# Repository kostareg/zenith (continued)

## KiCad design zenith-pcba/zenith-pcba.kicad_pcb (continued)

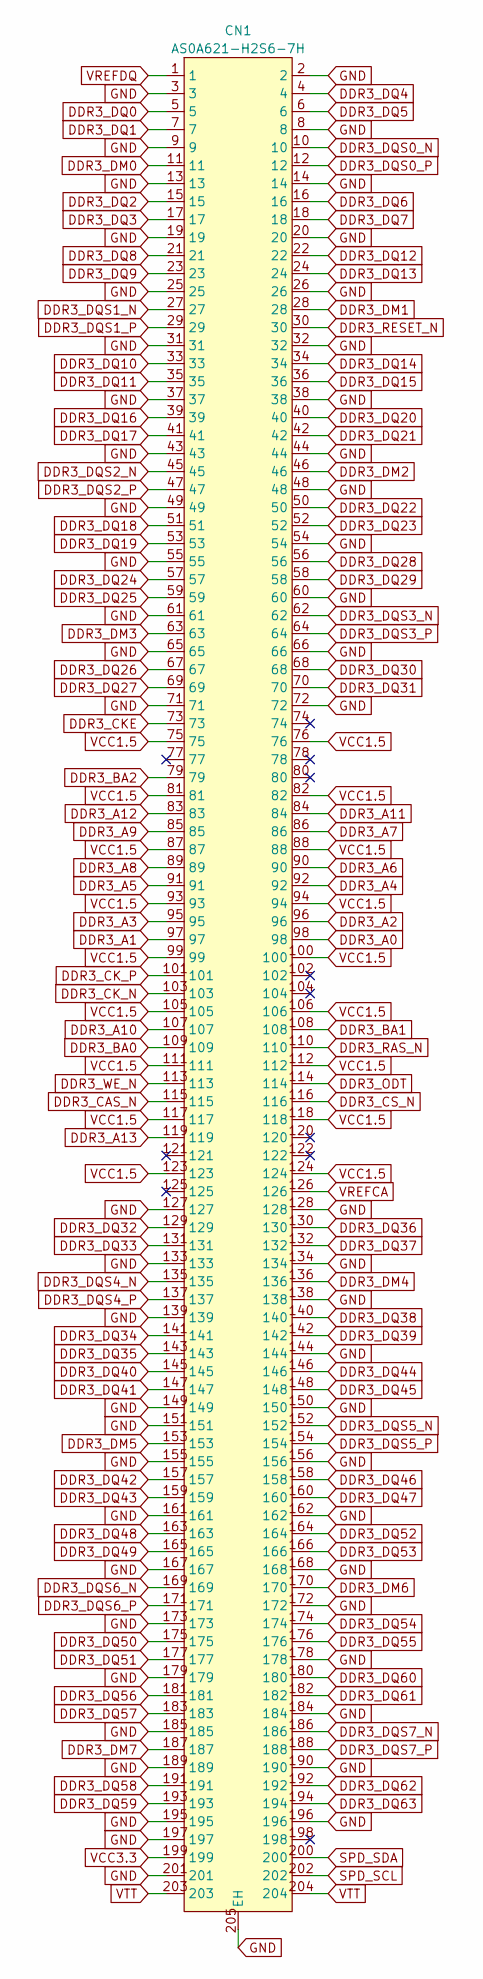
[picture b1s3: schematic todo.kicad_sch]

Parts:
CN1: AS0A621-H2S6-7H; CONN-SMD_204P-P0.60_AS0A621-H2S6-7H; MPN AS0A621-H2S6-7H; LCSC Part C225721

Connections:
DDR3_A0: CN1.98; also elsewhere on the board
DDR3_A1: CN1.97; also elsewhere on the board
DDR3_A2: CN1.96; also elsewhere on the board
DDR3_A3: CN1.95; also elsewhere on the board
DDR3_A4: CN1.92; also elsewhere on the board
DDR3_A5: CN1.91; also elsewhere on the board
DDR3_A6: CN1.90; also elsewhere on the board
DDR3_A7: CN1.86; also elsewhere on the board
DDR3_A8: CN1.89; also elsewhere on the board
DDR3_A9: CN1.85; also elsewhere on the board
DDR3_A10: CN1.107; also elsewhere on the board
DDR3_A11: CN1.84; also elsewhere on the board
DDR3_A12: CN1.83; also elsewhere on the board
DDR3_A13: CN1.119; also elsewhere on the board
DDR3_BA0: CN1.109; also elsewhere on the board
DDR3_BA1: CN1.108; also elsewhere on the board
DDR3_BA2: CN1.79; also elsewhere on the board
DDR3_CAS_N: CN1.115; also elsewhere on the board
DDR3_CKE: CN1.73; also elsewhere on the board
DDR3_CK_N: CN1.103; also elsewhere on the board
DDR3_CK_P: CN1.101; also elsewhere on the board
DDR3_CS_N: CN1.116; also elsewhere on the board
DDR3_DM0: CN1.11; also elsewhere on the board
DDR3_DM1: CN1.28; also elsewhere on the board
DDR3_DM2: CN1.46; also elsewhere on the board
DDR3_DM3: CN1.63; also elsewhere on the board
DDR3_DM4: CN1.136; also elsewhere on the board
DDR3_DM5: CN1.153; also elsewhere on the board
DDR3_DM6: CN1.170; also elsewhere on the board
DDR3_DM7: CN1.187; also elsewhere on the board
DDR3_DQ0: CN1.5; also elsewhere on the board
DDR3_DQ1: CN1.7; also elsewhere on the board
DDR3_DQ2: CN1.15; also elsewhere on the board
DDR3_DQ3: CN1.17; also elsewhere on the board
DDR3_DQ4: CN1.4; also elsewhere on the board
DDR3_DQ5: CN1.6; also elsewhere on the board
DDR3_DQ6: CN1.16; also elsewhere on the board
DDR3_DQ7: CN1.18; also elsewhere on the board
DDR3_DQ8: CN1.21; also elsewhere on the board
DDR3_DQ9: CN1.23; also elsewhere on the board
DDR3_DQ10: CN1.33; also elsewhere on the board
DDR3_DQ11: CN1.35; also elsewhere on the board
DDR3_DQ12: CN1.22; also elsewhere on the board
DDR3_DQ13: CN1.24; also elsewhere on the board
DDR3_DQ14: CN1.34; also elsewhere on the board
DDR3_DQ15: CN1.36; also elsewhere on the board
DDR3_DQ16: CN1.39; also elsewhere on the board
DDR3_DQ17: CN1.41; also elsewhere on the board
DDR3_DQ18: CN1.51; also elsewhere on the board
DDR3_DQ19: CN1.53; also elsewhere on the board
DDR3_DQ20: CN1.40; also elsewhere on the board
DDR3_DQ21: CN1.42; also elsewhere on the board
DDR3_DQ22: CN1.50; also elsewhere on the board
DDR3_DQ23: CN1.52; also elsewhere on the board
DDR3_DQ24: CN1.57; also elsewhere on the board
DDR3_DQ25: CN1.59; also elsewhere on the board
DDR3_DQ26: CN1.67; also elsewhere on the board
DDR3_DQ27: CN1.69; also elsewhere on the board
DDR3_DQ28: CN1.56; also elsewhere on the board
DDR3_DQ29: CN1.58; also elsewhere on the board
DDR3_DQ30: CN1.68; also elsewhere on the board
DDR3_DQ31: CN1.70; also elsewhere on the board
DDR3_DQ32: CN1.129; also elsewhere on the board
DDR3_DQ33: CN1.131; also elsewhere on the board
DDR3_DQ34: CN1.141; also elsewhere on the board
DDR3_DQ35: CN1.143; also elsewhere on the board
DDR3_DQ36: CN1.130; also elsewhere on the board
DDR3_DQ37: CN1.132; also elsewhere on the board
DDR3_DQ38: CN1.140; also elsewhere on the board
DDR3_DQ39: CN1.142; also elsewhere on the board
DDR3_DQ40: CN1.145; also elsewhere on the board
DDR3_DQ41: CN1.147; also elsewhere on the board
DDR3_DQ42: CN1.157; also elsewhere on the board
DDR3_DQ43: CN1.159; also elsewhere on the board
DDR3_DQ44: CN1.146; also elsewhere on the board
DDR3_DQ45: CN1.148; also elsewhere on the board
DDR3_DQ46: CN1.158; also elsewhere on the board
DDR3_DQ47: CN1.160; also elsewhere on the board
DDR3_DQ48: CN1.163; also elsewhere on the board
DDR3_DQ49: CN1.165; also elsewhere on the board
DDR3_DQ50: CN1.175; also elsewhere on the board
DDR3_DQ51: CN1.177; also elsewhere on the board
DDR3_DQ52: CN1.164; also elsewhere on the board
DDR3_DQ53: CN1.166; also elsewhere on the board
DDR3_DQ54: CN1.174; also elsewhere on the board
DDR3_DQ55: CN1.176; also elsewhere on the board
DDR3_DQ56: CN1.181; also elsewhere on the board
DDR3_DQ57: CN1.183; also elsewhere on the board
DDR3_DQ58: CN1.191; also elsewhere on the board
DDR3_DQ59: CN1.193; also elsewhere on the board
DDR3_DQ60: CN1.180; also elsewhere on the board
DDR3_DQ61: CN1.182; also elsewhere on the board
DDR3_DQ62: CN1.192; also elsewhere on the board
DDR3_DQ63: CN1.194; also elsewhere on the board
DDR3_DQS0_N: CN1.10; also elsewhere on the board
DDR3_DQS0_P: CN1.12; also elsewhere on the board
DDR3_DQS1_N: CN1.27; also elsewhere on the board
DDR3_DQS1_P: CN1.29; also elsewhere on the board
DDR3_DQS2_N: CN1.45; also elsewhere on the board
DDR3_DQS2_P: CN1.47; also elsewhere on the board
DDR3_DQS3_N: CN1.62; also elsewhere on the board
DDR3_DQS3_P: CN1.64; also elsewhere on the board
DDR3_DQS4_N: CN1.135; also elsewhere on the board
DDR3_DQS4_P: CN1.137; also elsewhere on the board
DDR3_DQS5_N: CN1.152; also elsewhere on the board
DDR3_DQS5_P: CN1.154; also elsewhere on the board
DDR3_DQS6_N: CN1.169; also elsewhere on the board
DDR3_DQS6_P: CN1.171; also elsewhere on the board
DDR3_DQS7_N: CN1.186; also elsewhere on the board
DDR3_DQS7_P: CN1.188; also elsewhere on the board
DDR3_ODT: CN1.114; also elsewhere on the board
DDR3_RAS_N: CN1.110; also elsewhere on the board
DDR3_RESET_N: CN1.30; also elsewhere on the board
DDR3_WE_N: CN1.113; also elsewhere on the board
GND: CN1.2, CN1.3, CN1.8, CN1.9, CN1.13, CN1.14, CN1.19, CN1.20, CN1.25, CN1.26, CN1.31, CN1.32, CN1.37, CN1.38, CN1.43, CN1.44, CN1.48, CN1.49, CN1.54, CN1.55, CN1.60, CN1.61, CN1.65, CN1.66, CN1.71, CN1.72, CN1.127, CN1.128, CN1.133, CN1.134, CN1.138, CN1.139, CN1.144, CN1.149, CN1.150, CN1.151, CN1.155, CN1.156, CN1.161, CN1.162, CN1.167, CN1.168, CN1.172, CN1.173, CN1.178, CN1.179, CN1.184, CN1.185, CN1.189, CN1.190, CN1.195, CN1.196, CN1.197, CN1.201, CN1.205 (EH); also elsewhere on the board
SPD_SCL: CN1.202
SPD_SDA: CN1.200
VCC1.5: CN1.75, CN1.76, CN1.81, CN1.82, CN1.87, CN1.88, CN1.93, CN1.94, CN1.99, CN1.100, CN1.105, CN1.106, CN1.111, CN1.112, CN1.117, CN1.118, CN1.123, CN1.124
VCC3.3: CN1.199; also elsewhere on the board
VREFCA: CN1.126
VREFDQ: CN1.1
VTT: CN1.203, CN1.204

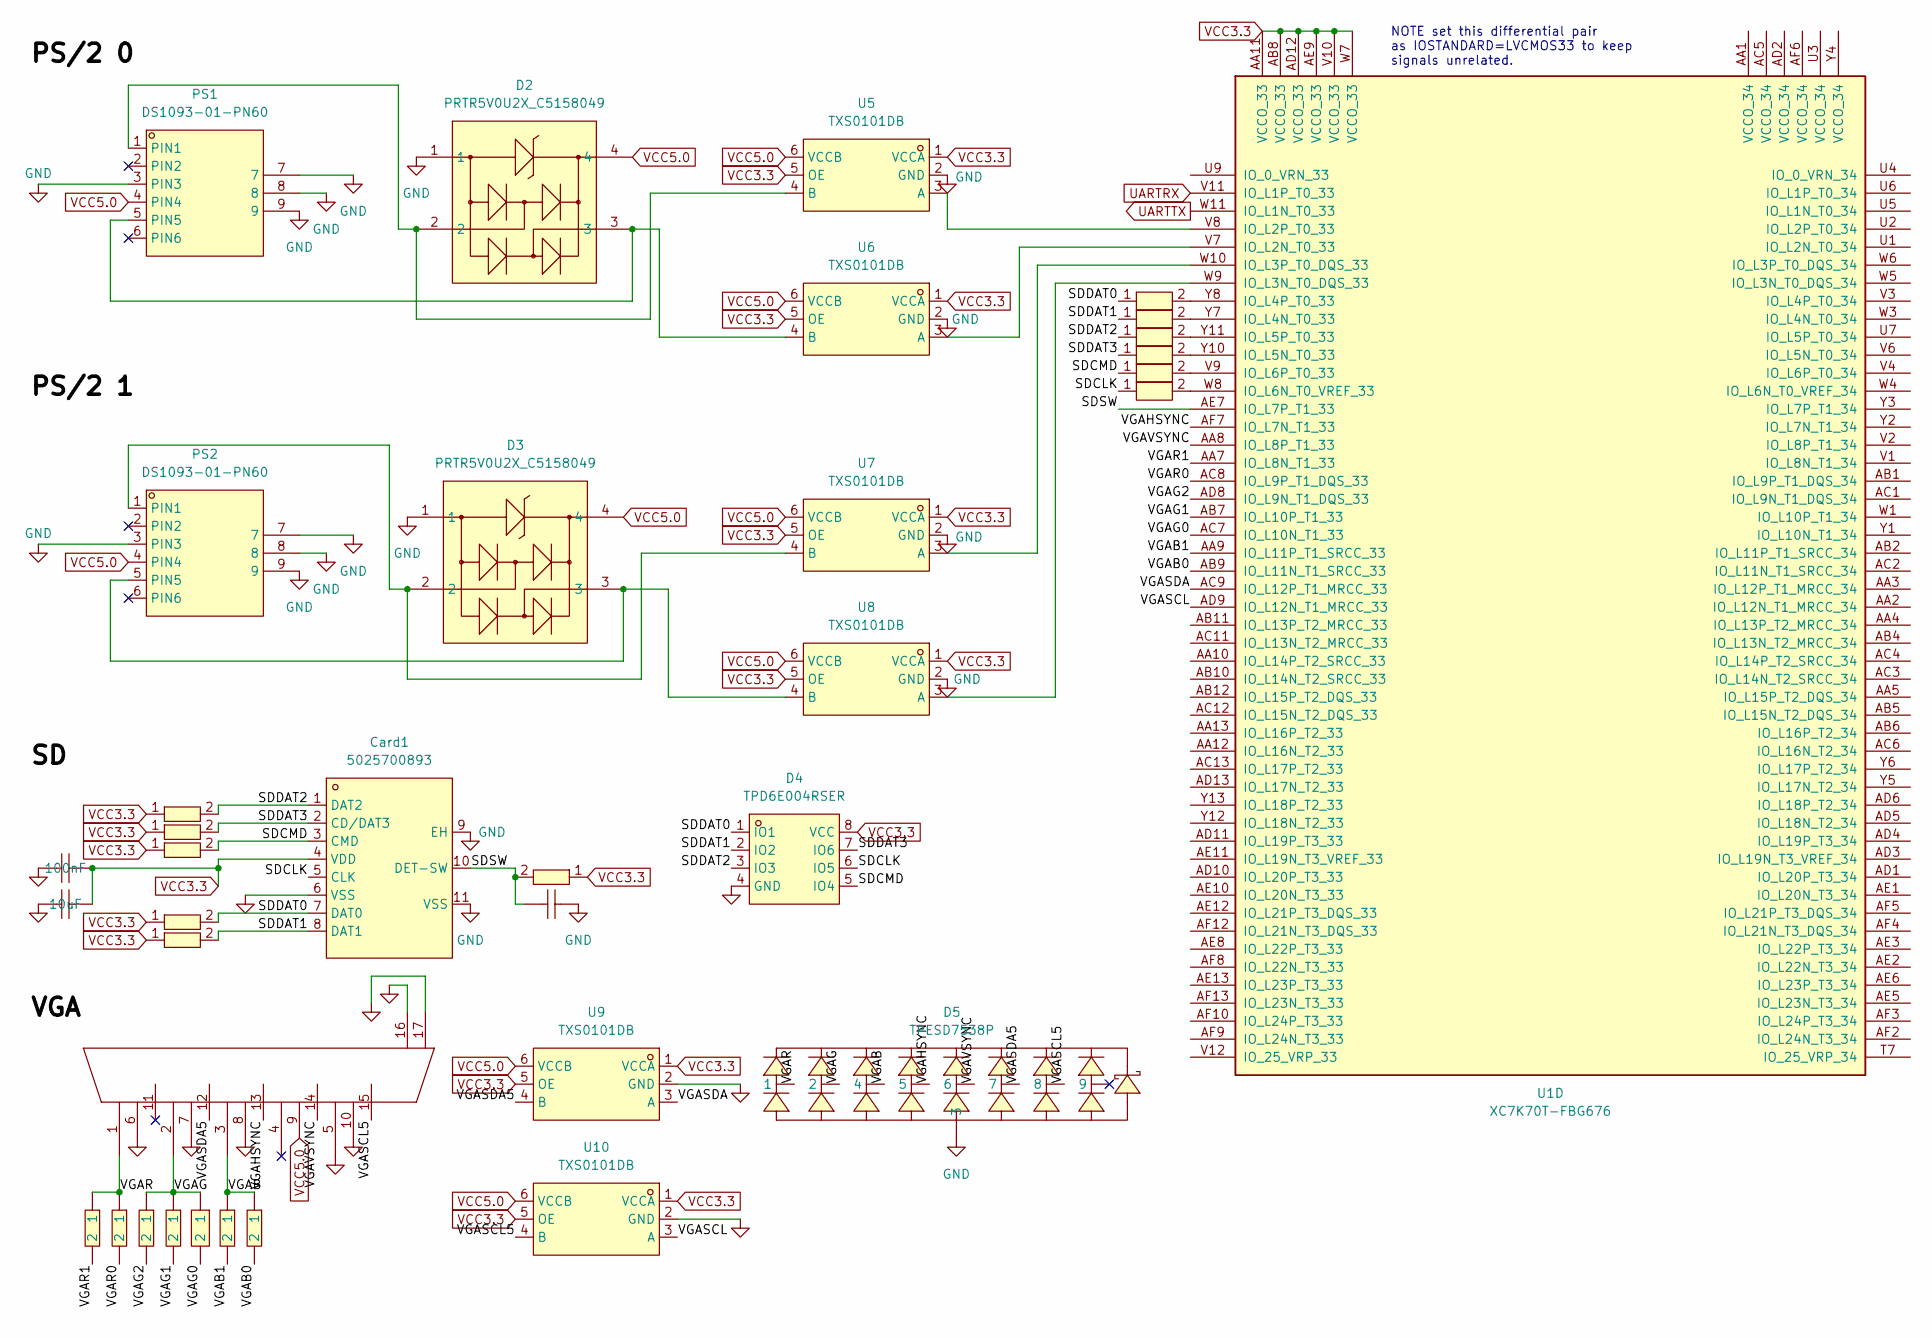
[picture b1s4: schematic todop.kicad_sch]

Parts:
C8, C9: CL10B104KA8NNNC; C0603; MPN CL10B104KA8NNNC; LCSC Part C1590
C10: CC0603MRX5R7BB106; C0603; MPN CC0603MRX5R7BB106; LCSC Part C109457
Card1: 5025700893; TF-SMD_5025700893; MPN 5025700893; LCSC Part C429846
D2, D3: PRTR5V0U2X_C5158049; SOT-143_L2.9-W1.3-P1.92-LS2.3-BL; MPN PRTR5V0U2X; LCSC Part C5158049
D4: TPD6E004RSER; UQFN-8_L1.5-W1.5-P0.50-TL; MPN TPD6E004RSER; LCSC Part C1973052
D5: TPESD7538P; DFN3810-9_L3.8-W1.0-P0.9; MPN TPESD7538P; LCSC Part C970014
DSub1: DS1038-15FBNSIA74-0CC; DSUB-TH_DS1038-15FBNSIA74-0CC; MPN DS1038-15FBNSiA74-0CC; LCSC Part C75754
PS1, PS2: DS1093-01-PN60; CONN-TH_DS1093-01-PN60; MPN DS1093-01-PN60; LCSC Part C77848
R5, R6, R7, R8, R9, R16: RC0402FR-0710KL; R0402; MPN RC0402FR-0710KL; LCSC Part C60490
R10, R11, R12, R13, R14, R15: RC0402FR-0722R1L; R0402; MPN RC0402FR-0722R1L; LCSC Part C327363
R17, R19, R21: RC0402JR-07510RL; R0402; MPN RC0402JR-07510RL; LCSC Part C137860
R18, R20, R22: RC0402FR-071K02L; R0402; MPN RC0402FR-071K02L; LCSC Part C163485
R23: RC0402DR-072K05L; R0402; MPN RC0402DR-072K05L; LCSC Part C471776
U1: XC7K70T-FBG676; FBGA-676_L27.0-W27.0-R26-C26-P1.00-BL
U5, U6, U7, U8, U9, U10: TXS0101DB; SOT-23-6_L2.9-W1.6-P0.95-LS2.9-BL; MPN TXS0101DB(LX); LCSC Part C22469953

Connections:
/IO/SDCLK: Card1.5 (CLK), D4.6 (IO5), R15.1
/IO/SDCMD: Card1.3 (CMD), D4.5 (IO4), R7.2, R14.1
/IO/SDDAT0: Card1.7 (DAT0), D4.1 (IO1), R8.2, R10.1
/IO/SDDAT1: Card1.8 (DAT1), D4.2 (IO2), R9.2, R11.1
/IO/SDDAT2: Card1.1 (DAT2), D4.3 (IO3), R5.2, R12.1
/IO/SDDAT3: Card1.2 (CD/DAT3), D4.7 (IO6), R6.2, R13.1
/IO/SDSW: C8.1, Card1.10 (DET-SW), R16.2, U1.AE7 (IO_L7P_T1_33)
/IO/VGAB: D5.4, DSub1.3, R21.1, R22.1
/IO/VGAB0: R22.2, U1.AB9 (IO_L11N_T1_SRCC_33)
/IO/VGAB1: R21.2, U1.AA9 (IO_L11P_T1_SRCC_33)
/IO/VGAG: D5.2, DSub1.2, R19.1, R20.1, R23.1
/IO/VGAG0: R23.2, U1.AC7 (IO_L10N_T1_33)
/IO/VGAG1: R20.2, U1.AB7 (IO_L10P_T1_33)
/IO/VGAG2: R19.2, U1.AD8 (IO_L9N_T1_DQS_33)
/IO/VGAHSYNC: D5.5, DSub1.13, U1.AF7 (IO_L7N_T1_33)
/IO/VGAR: D5.1, DSub1.1, R17.1, R18.1
/IO/VGAR0: R18.2, U1.AC8 (IO_L9P_T1_DQS_33)
/IO/VGAR1: R17.2, U1.AA7 (IO_L8N_T1_33)
/IO/VGASCL: U1.AD9 (IO_L12N_T1_MRCC_33), U10.3 (A)
/IO/VGASCL5: D5.8, DSub1.15, U10.4 (B)
/IO/VGASDA: U1.AC9 (IO_L12P_T1_MRCC_33), U9.3 (A)
/IO/VGASDA5: D5.7, DSub1.12, U9.4 (B)
/IO/VGAVSYNC: D5.6, DSub1.14, U1.AA8 (IO_L8P_T1_33)
GND: C8.2, C9.1, C10.1, Card1.6 (VSS), Card1.9 (EH), Card1.11 (VSS), D2.1, D3.1, D4.4 (GND), D5.3, DSub1.5, DSub1.6, DSub1.7, DSub1.8, DSub1.10, DSub1.16, DSub1.17, PS1.3 (PIN3), PS1.7, PS1.8, PS1.9, PS2.3 (PIN3), PS2.7, PS2.8, PS2.9, U5.2 (GND), U6.2 (GND), U7.2 (GND), U8.2 (GND), U9.2 (GND), U10.2 (GND); also elsewhere on the board
unnamed: D2.2, PS1.1 (PIN1), U5.4 (B)
unnamed: D2.3, PS1.5 (PIN5), U6.4 (B)
unnamed: D3.2, PS2.1 (PIN1), U7.4 (B)
unnamed: D3.3, PS2.5 (PIN5), U8.4 (B)
unnamed: U1.V7 (IO_L2N_T0_33), U6.3 (A)
unnamed: U1.V8 (IO_L2P_T0_33), U5.3 (A)
unnamed: U1.W9 (IO_L3N_T0_DQS_33), U8.3 (A)
unnamed: U1.W10 (IO_L3P_T0_DQS_33), U7.3 (A)
unnamed: R11.2, U1.Y7 (IO_L4N_T0_33)
unnamed: R10.2, U1.Y8 (IO_L4P_T0_33)
unnamed: R13.2, U1.Y10 (IO_L5N_T0_33)
unnamed: R12.2, U1.Y11 (IO_L5P_T0_33)
unnamed: R15.2, U1.W8 (IO_L6N_T0_VREF_33)
unnamed: R14.2, U1.V9 (IO_L6P_T0_33)
UARTRX: U1.V11 (IO_L1P_T0_33); also elsewhere on the board
UARTTX: U1.W11 (IO_L1N_T0_33); also elsewhere on the board
VCC3.3: C9.2, C10.2, Card1.4 (VDD), D4.8 (VCC), R5.1, R6.1, R7.1, R8.1, R9.1, R16.1, U1.AA11 (VCCO_33), U1.AB8 (VCCO_33), U1.AD12 (VCCO_33), U1.AE9 (VCCO_33), U1.V10 (VCCO_33), U1.W7 (VCCO_33), U5.1 (VCCA), U5.5 (OE), U6.1 (VCCA), U6.5 (OE), U7.1 (VCCA), U7.5 (OE), U8.1 (VCCA), U8.5 (OE), U9.1 (VCCA), U9.5 (OE), U10.1 (VCCA), U10.5 (OE); also elsewhere on the board
VCC5.0: D2.4, D3.4, DSub1.9, PS1.4 (PIN4), PS2.4 (PIN4), U5.6 (VCCB), U6.6 (VCCB), U7.6 (VCCB), U8.6 (VCCB), U9.6 (VCCB), U10.6 (VCCB); also elsewhere on the board

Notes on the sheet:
NOTE set this differential pair as IOSTANDARD=LVCMOS33 to keep signals unrelated.

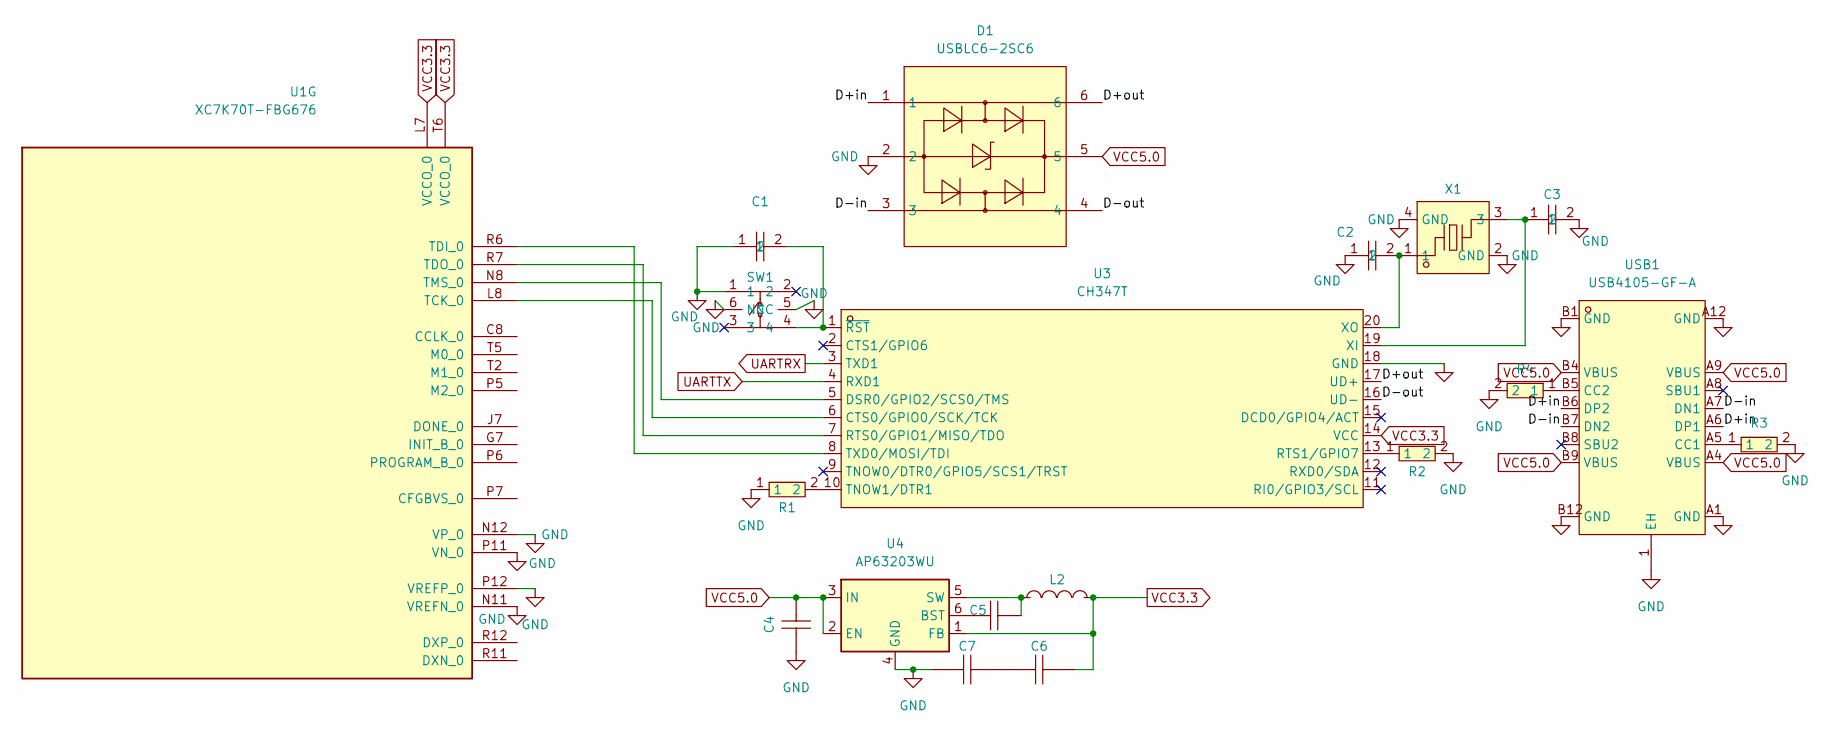
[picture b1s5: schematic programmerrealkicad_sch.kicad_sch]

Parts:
C1, C5: CL10B104KA8NNNC; C0603; MPN CL10B104KA8NNNC; LCSC Part C1590
C2, C3: 0402CG220J500NT; C0402; MPN 0402CG220J500NT; LCSC Part C1555
C4: CC0603MRX5R7BB106; C0603; MPN CC0603MRX5R7BB106; LCSC Part C109457
C6, C7: CC1206KKX7R6BB226; C1206; MPN CC1206KKX7R6BB226; LCSC Part C110045
D1: USBLC6-2SC6; SOT-23-6_L2.9-W1.6-P0.95-LS2.8-BL; MPN USBLC6-2SC6; LCSC Part C7519
L2: SWPA4030S3R3MT; IND-SMD_L4.0-W4.0_SMNR4012; MPN SWPA4030S3R3MT; LCSC Part C15269
R1, R2: RC0603FR-074K7L; R0603; MPN RC0603FR-074K7L; LCSC Part C99782
R3, R4: RC0603JR-075K1L; R0603; MPN RC0603JR-075K1L; LCSC Part C14677
SW1: G4R152312; SW-SMD_4P-L5.2-W5.2-P3.70-LS6.4_UK-B0233XX; MPN G4R152312; LCSC Part C49393646
U1: XC7K70T-FBG676; FBGA-676_L27.0-W27.0-R26-C26-P1.00-BL
U3: CH347T; TSSOP-20_L6.5-W4.4-P0.65-LS6.4-BL; MPN CH347T; LCSC Part C5122332
U4: AP63203WU; TSOT-23-6
USB1: USB4105-GF-A; TYPE-C-SMD_SBC-160S1A-20-S412; MPN USB4105-GF-A; LCSC Part C3020560
X1: SX5B8.000F1520F30; CYSTAL-SMD_4P-L5.0-W3.2-BL; MPN SX5B8.000F1520F30; LCSC Part C2901621

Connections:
/Programmer/D+in: D1.1, USB1.A6 (DP1), USB1.B6 (DP2)
/Programmer/D+out: D1.6, U3.17 (UD+)
/Programmer/D-in: D1.3, USB1.A7 (DN1), USB1.B7 (DN2)
/Programmer/D-out: D1.4, U3.16 (UD-)
GND: C1.1, C2.1, C3.2, C4.2, C7.1, D1.2, R1.1, R2.2, R3.2, R4.2, SW1.1, SW1.5 (NC), SW1.6 (NC), U1.N11 (VREFN_0), U1.N12 (VP_0), U1.P11 (VN_0), U1.P12 (VREFP_0), U3.18 (GND), U4.4 (GND), USB1.1 (EH), USB1.A1 (GND), USB1.A12 (GND), USB1.B1 (GND), USB1.B12 (GND), X1.2 (GND), X1.4 (GND); also elsewhere on the board
unnamed: C6.1, C7.2
unnamed: U1.L8 (TCK_0), U3.6 (CTS0/GPIO0/SCK/TCK)
unnamed: U1.R6 (TDI_0), U3.8 (TXD0/MOSI/TDI)
unnamed: U1.R7 (TDO_0), U3.7 (RTS0/GPIO1/MISO/TDO)
unnamed: U1.N8 (TMS_0), U3.5 (DSR0/GPIO2/SCS0/TMS)
unnamed: R2.1, U3.13 (RTS1/GPIO7)
unnamed: R1.2, U3.10 (TNOW1/DTR1)
unnamed: C3.1, U3.19 (XI), X1.3
unnamed: C2.2, U3.20 (XO), X1.1
unnamed: C1.2, SW1.4, U3.1 (~RST)
unnamed: C5.1, U4.6 (BST)
unnamed: C5.2, L2.1, U4.5 (SW)
unnamed: R3.1, USB1.A5 (CC1)
unnamed: R4.1, USB1.B5 (CC2)
UARTRX: U3.3 (TXD1); also elsewhere on the board
UARTTX: U3.4 (RXD1); also elsewhere on the board
VCC3.3: C6.2, L2.2, U1.L7 (VCCO_0), U1.T6 (VCCO_0), U3.14 (VCC), U4.1 (FB); also elsewhere on the board
VCC5.0: C4.1, D1.5, U4.2 (EN), U4.3 (IN), USB1.A4 (VBUS), USB1.A9 (VBUS), USB1.B4 (VBUS), USB1.B9 (VBUS); also elsewhere on the board

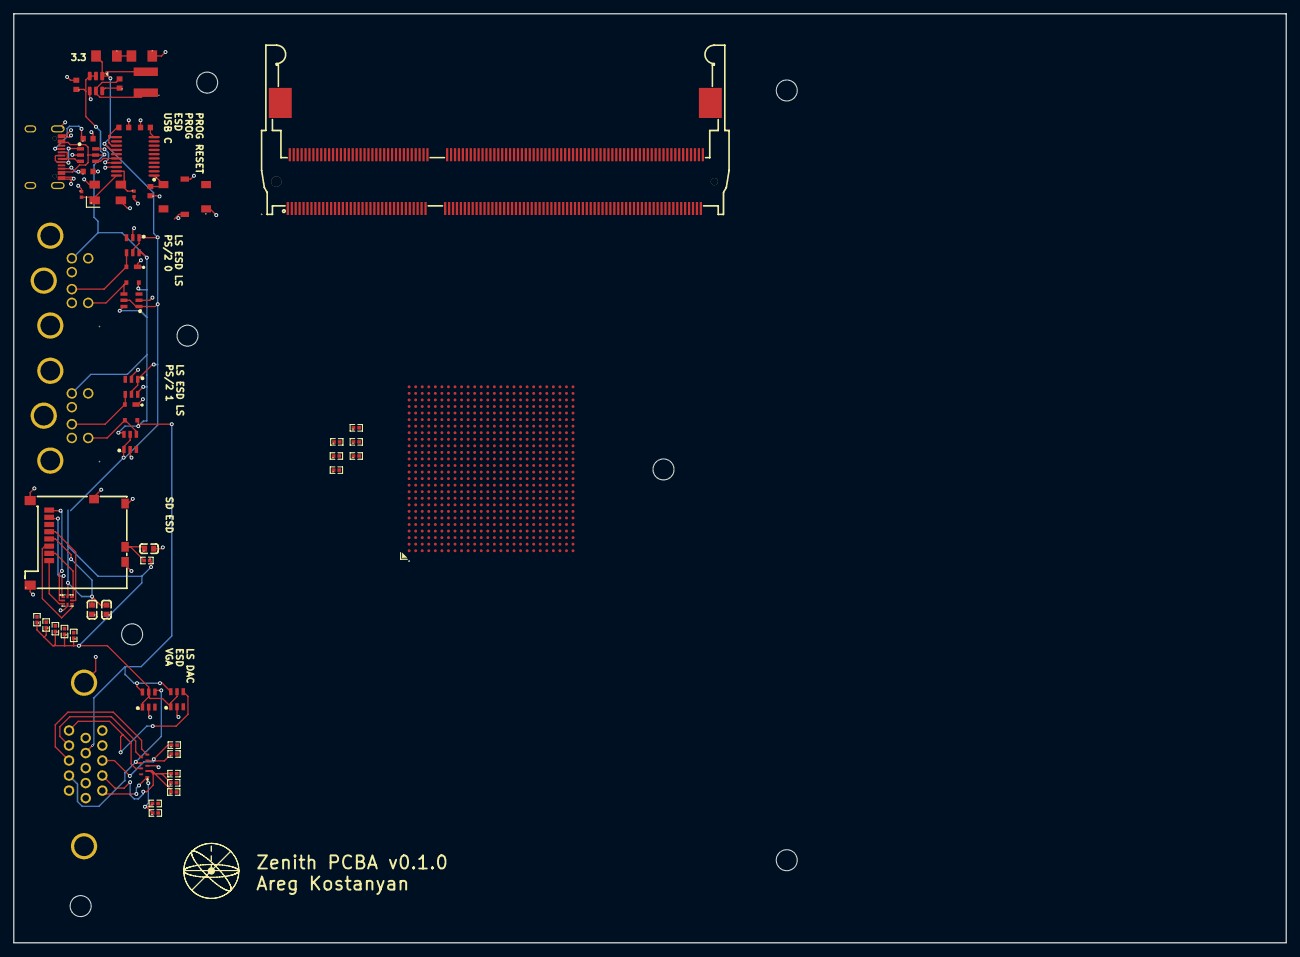
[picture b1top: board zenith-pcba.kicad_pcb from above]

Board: 2 copper layers, 194.1 x 141.7 mm, 56 parts (0 on the bottom side), 178 nets.

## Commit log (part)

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2026-04-28 feat: initial commit
2026-04-28 feat: set up emulator
2026-04-29 feat: implement addition instructions
2026-04-29 feat(web): basic instruction entry
2026-05-10 feat(emulator): basic implementation of ISA
2026-05-10 chore(emulator): tidy coding style
2026-05-10 feat(web): basic interface
2026-05-15 chore: add nix configuration
2026-05-15 fix(emulator): compilation process for wasm
2026-05-15 chore: remove dark theme
2026-05-15 chore: embind
2026-05-19 docs: add references
2026-05-19 chore: generate typescript straight from embind
2026-05-19 chore(web): format
2026-05-20 docs: add system calls and executable format
2026-05-20 docs: framebuffer
2026-05-20 docs: keyboard
2026-05-20 chore: unify design document
2026-05-20 chore: clean up emulator
2026-05-20 chore: set up assembler
2026-05-20 ci: set up
2026-05-20 ci: cache nix store
2026-05-20 ci: pages permissions
2026-05-20 docs: clean up
2026-05-20 feat(asm): basic lexer
2026-05-20 feat(asm): lex numbers
2026-05-20 feat(asm): parser
2026-05-20 feat(asm): compiler
2026-05-20 feat(asm): formatter
2026-05-20 test: assembler
2026-05-21 chore: update example zasm
2026-05-21 feat(web): assembly
2026-05-21 feat(web): syntax highlighting
2026-05-22 feat(emulator): framebuffer
2026-05-22 feat(hardware): initial setup
2026-05-22 chore: migrate to zenith-assembler naming
2026-05-25 feat(hardware): states
2026-05-25 feat(hardware): basic fake memory
2026-05-29 feat(hardware): register file
2026-05-29 feat(hardware): memory controller
2026-05-29 feat(hardware): alu
2026-05-29 feat(hardware): instruction list
2026-05-29 chore: split up sources
2026-05-29 feat(hardware): basic addition program
2026-05-29 fix(hardware): use alu for pc increments
2026-05-29 feat(hardware): rest of ALU-related instructions
2026-05-29 feat: shifts and not operator
2026-05-29 feat(hardware): memory instructions
2026-05-29 feat(hardware): control flow instructions
2026-05-29 fix(hardware): remove sim sources from elaborated design
2026-05-29 feat(hardware): system rdl keyboard mmio setup
2026-05-29 feat(hardware): keyboard fifo
2026-05-29 fix(hardware): keyboard mmio rdl base address
2026-05-29 ci: generate systemrdl to website
2026-05-29 chore: update dependency list
2026-05-29 ci: fix systemrdl workflow
2026-06-02 test: keyboard
2026-06-04 feat(assembler): generate zelf
2026-06-12 feat(compiler): setup
2026-06-12 ci(compiler): build and test
2026-06-12 feat(compiler): lexer
2026-06-12 chore(compiler): format
2026-06-16 feat(compiler): preprocessor
2026-06-17 feat(compiler): parser
2026-06-17 feat(compiler): code generator
2026-06-17 feat(web): zenith C
2026-06-17 chore(libc): set up zenith libc
2026-06-17 feat(web): instructions per frame graph
2026-06-17 fix(compiler): register clobber when doing comparison on same register
2026-06-17 feat: global variables
2026-06-17 feat(compiler): string literals
2026-06-17 feat(web): full screen framebuffer
2026-06-17 feat(web): system includes
2026-06-17 feat(web): minimap
2026-06-17 fix(web): relative path for libc
2026-06-17 feat(libc): print newlines
2026-06-17 feat(libc): print integers
2026-06-17 feat(libc): string comparisons
2026-06-17 feat(libc): strlen
2026-06-17 chore(libc): cleanup
2026-06-18 feat(libc): ipow and isalnum-related functions
2026-06-18 feat(kernel): read keyboard fifo
2026-06-18 feat(libc): scanf
2026-06-18 fix(libc): scanf newlines
